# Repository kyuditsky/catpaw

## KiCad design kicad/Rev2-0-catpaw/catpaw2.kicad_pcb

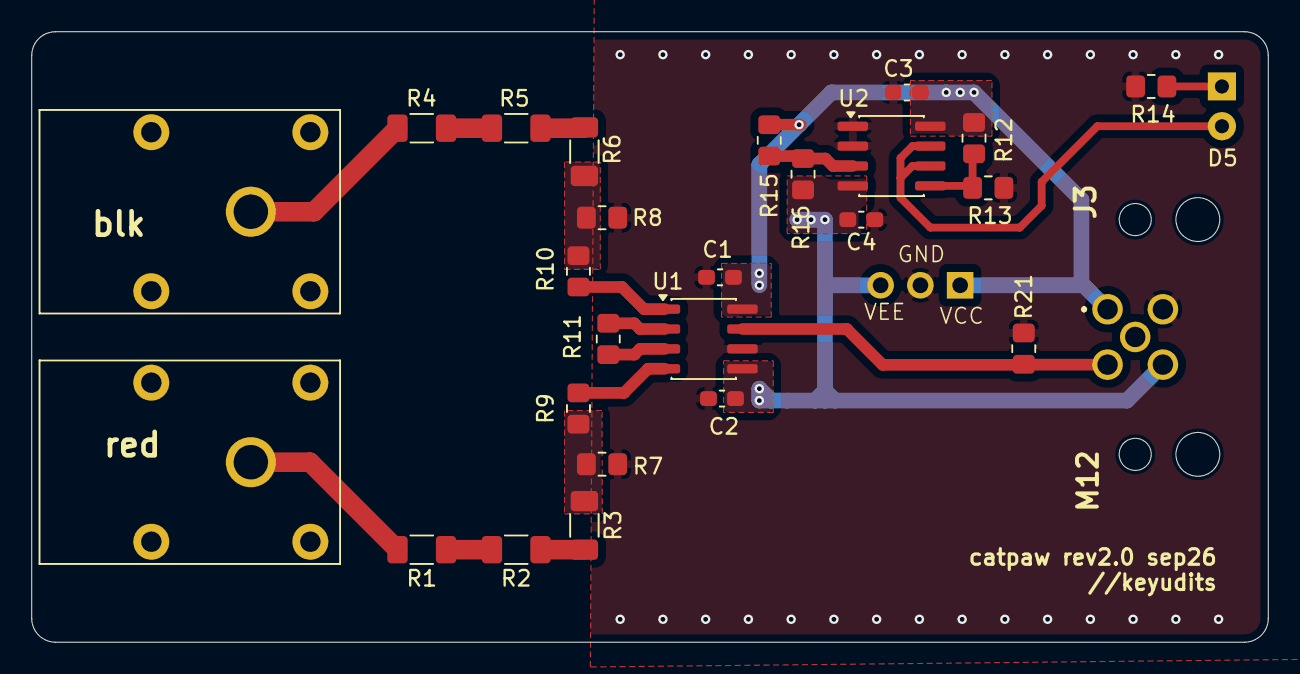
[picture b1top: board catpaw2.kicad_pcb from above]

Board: 2 copper layers, 79.0 x 39.0 mm, 28 parts (1 on the bottom side), 20 nets.

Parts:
C1, C2, C3, C4: 104; C_0603_1608Metric_Pad1.08x0.95mm_HandSolder
D5: LED; LED_D3.0mm_Horizontal_O1.27mm_Z2.0mm
J1: Conn_01x01_Socket_red; Banana_Jack_S_RA_73099
J2: Conn_01x01_Socket_black; Banana_Jack_S_RA_73099
J3: m12,Acode,5pin,femalesocket (to beckhoff input); M12A05PFFRSF7003
J4: Conn_01x03_Pin; PinHeader_1x03_P2.54mm_Vertical
R1, R2, R3, R4, R5, R6: 1M; R_1206_3216Metric_Pad1.30x1.75mm_HandSolder
R7, R8: 30.1k; R_0805_2012Metric_Pad1.20x1.40mm_HandSolder
R9, R10, R15, R16: 10k; R_0805_2012Metric_Pad1.20x1.40mm_HandSolder
R11: 1M; R_0805_2012Metric_Pad1.20x1.40mm_HandSolder
R12: 4.7k; R_0805_2012Metric_Pad1.20x1.40mm_HandSolder
R13: 2.2k; R_0805_2012Metric_Pad1.20x1.40mm_HandSolder
R14: 1k; R_0805_2012Metric_Pad1.20x1.40mm_HandSolder
R21: load; R_0805_2012Metric_Pad1.20x1.40mm_HandSolder
U1: INA826; SOIC-8_3.9x4.9mm_P1.27mm
U2: LM1458mx; SOIC-8_3.9x4.9mm_P1.27mm

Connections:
/In+ Analog Input: J3.2, R21.1, U1.7
/VACin+: J1.1, R1.2
/VACin-: J2.1, R4.2
/Vcc+: C1.2, C3.2, J3.1, J4.1, R12.2, R15.2, U1.8 (Vs+), U2.8 (V+)
/Vcc-: C2.2, C4.2, J3.3, J4.3, R16.1, U1.5 (Vs-), U2.4 (V-)
GND: C1.1, C2.1, C3.1, C4.1, J3.4, J4.2, R7.1, R8.2, R13.2, R14.2, R21.2, U1.6 (Ref), U2.1, U2.2 (-)
unnamed: D5.2 (A), U2.6 (-), U2.7
unnamed: D5.1 (K), R14.1
unnamed: R1.1, R2.2
unnamed: R2.1, R3.2
unnamed: R3.1, R7.2, R9.1
unnamed: R4.1, R5.2
unnamed: R5.1, R6.2
unnamed: R6.1, R8.1, R10.1
unnamed: R11.1, U1.3 (Rg)
unnamed: R11.2, U1.2 (Rg)
unnamed: R9.2, U1.4 (+)
unnamed: R10.2, U1.1 (-)
unnamed: R15.1, R16.2, U2.3 (+)
unnamed: R12.1, R13.1, U2.5 (+)

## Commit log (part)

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2026-05-15 added images folder
2026-05-15 modified gitignore
